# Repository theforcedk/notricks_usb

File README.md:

# notricks_usb
Pentest USB

Order the boards here http://dirtypcbs.com/store/designer/details/8489/1041/atmega32u4-development-board or upload to OSH Park

Download the Sparkfun bootloader (Caterina-promicro16.hex) located at https://github.com/dudanov/sparkfun-promicro-caterina-bootloader/tree/e15665e847b4d9003d69fccb293572aa5e1aae71

```
Burn fuses for external crystal (0 devision)
*Extended*: 0xcb
*High*: 0xd8
*Low*: 0xff
```

```
avrdude -p atmega32u4 -c atmelice_isp -U flash:w:Caterina-promicro16.hex -U efuse:w:0xcb:m -U hfuse:w:0xd8:m -U lfuse:w:0xff:m
```

Open the schematic in EAGLE for actual package sizes, but in general: resistors = 0603, capacitors = 0805

```
1x Atmega32u4 IC
2x 22R resistor
2x 1K resistor
1x 10K resistor
7x 100nF capacitor
1x 1uF capacitor
1x 10uF capacitor
2x LEDs
1x 16MHz crystal
2x 22pF capacitor
1x 2x3 header
Optional: 2x SMD jumper for HWB+VCC
```

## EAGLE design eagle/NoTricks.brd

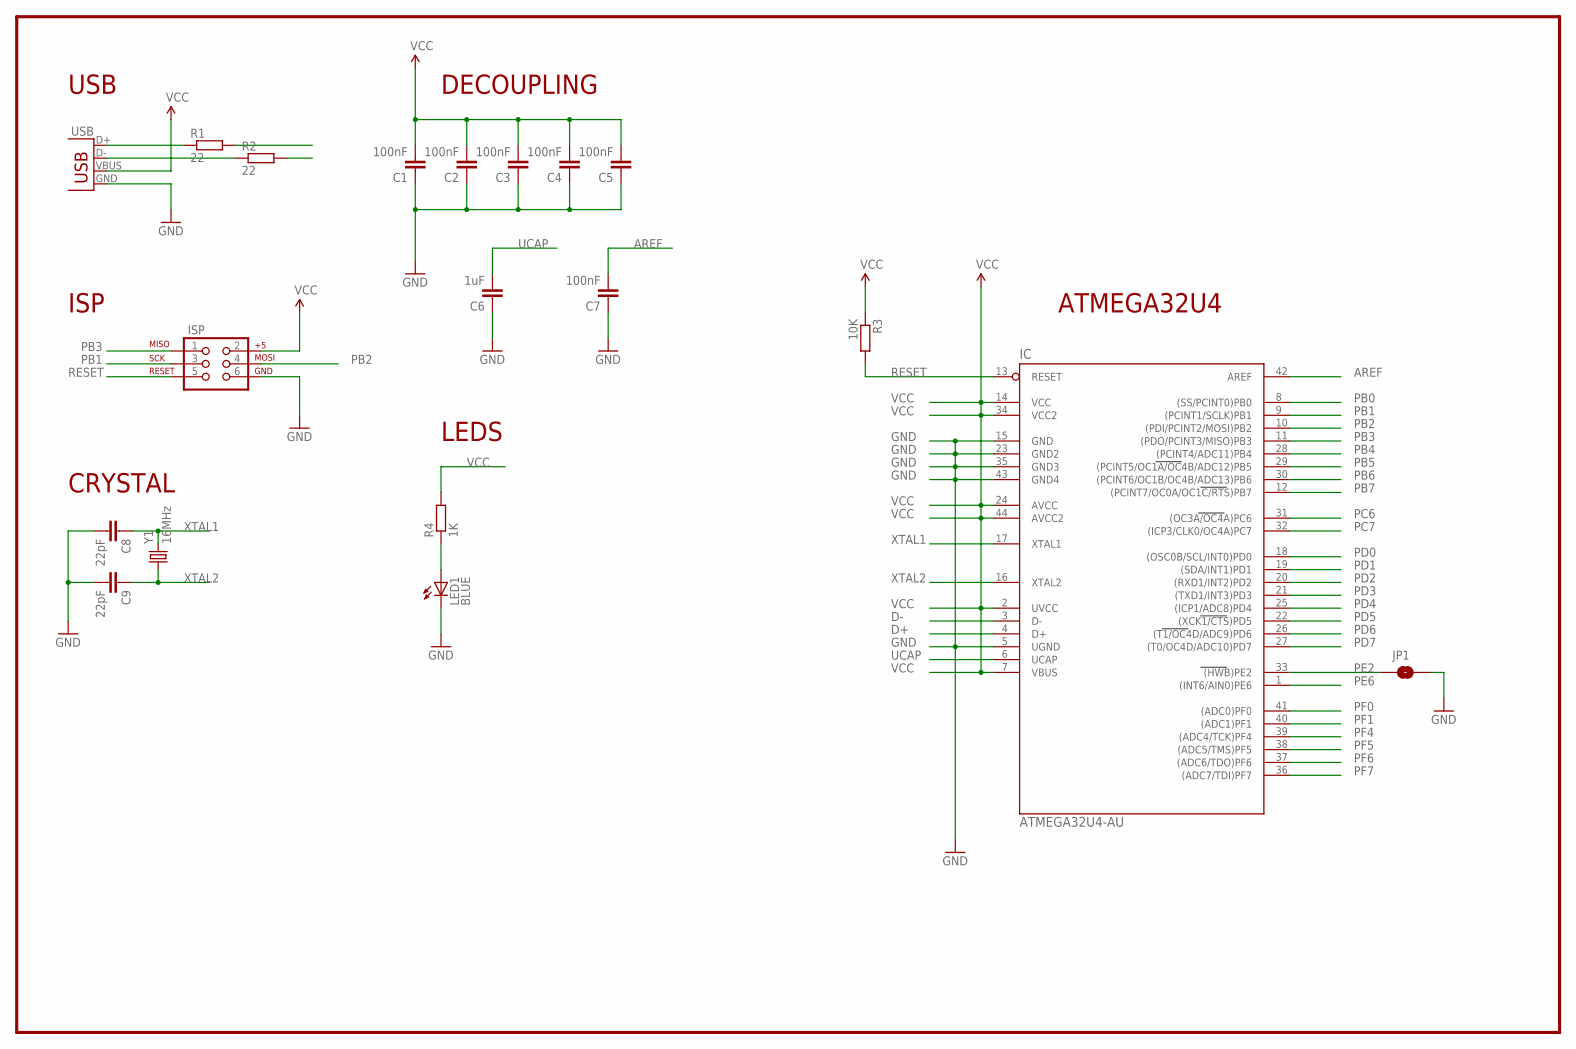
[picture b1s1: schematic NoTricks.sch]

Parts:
C1, C2, C3, C4, C5, C7: 100nF; C0805
C6: 1uF; C0805
C8, C9: 22pF; C0805
IC: ATMEGA32U4-AU; TQFP44
ISP: AVR_SPI_PRG_6PTH; 2X3
JP1: JUMPER-PAD-2-NO; PAD-JUMPER-2-NO_NO_SILK
LED1: BLUE; LED-1206
R1, R2: 22; R0603
R3: 10K; R0603
R4: 1K; R0603
USB: USB-A-H
Y1: 16MHz; CRYSTAL-SMD-5X3

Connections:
AREF: C7.2, IC.42 (AREF)
D+: IC.4 (D+), R1.2
D-: IC.3 (D-), R2.2
GND: C1.1, C2.1, C3.1, C4.1, C5.1, C6.1, C7.1, C8.2, C9.2, IC.5 (UGND), IC.15 (GND), IC.23 (GND2), IC.35 (GND3), IC.43 (GND4), ISP.6, JP1.2, LED1.C, USB.GND
unnamed: R1.1, USB.D+
unnamed: LED1.A, R4.1
unnamed: R2.1, USB.D-
PB0: IC.8 ((SS/PCINT0)PB0)
PB1: IC.9 ((PCINT1/SCLK)PB1), ISP.3
PB2: IC.10 ((PDI/PCINT2/MOSI)PB2), ISP.4
PB3: IC.11 ((PDO/PCINT3/MISO)PB3), ISP.1
PB4: IC.28 ((PCINT4/ADC11)PB4)
PB5: IC.29 ((PCINT5/OC1A/OC4B/ADC12)PB5)
PB6: IC.30 ((PCINT6/OC1B/OC4B/ADC13)PB6)
PB7: IC.12 ((PCINT7/OC0A/OC1C/RTS)PB7)
PC6: IC.31 ((OC3A/OC4A)PC6)
PC7: IC.32 ((ICP3/CLK0/OC4A)PC7)
PD0: IC.18 ((OSC0B/SCL/INT0)PD0)
PD1: IC.19 ((SDA/INT1)PD1)
PD2: IC.20 ((RXD1/INT2)PD2)
PD3: IC.21 ((TXD1/INT3)PD3)
PD4: IC.25 ((ICP1/ADC8)PD4)
PD5: IC.22 ((XCK1/CTS)PD5)
PD6: IC.26 ((T1/OC4D/ADC9)PD6)
PD7: IC.27 ((T0/OC4D/ADC10)PD7)
PE2: IC.33 ((HWB)PE2), JP1.1
PE6: IC.1 ((INT6/AIN0)PE6)
PF0: IC.41 ((ADC0)PF0)
PF1: IC.40 ((ADC1)PF1)
PF4: IC.39 ((ADC4/TCK)PF4)
PF5: IC.38 ((ADC5/TMS)PF5)
PF6: IC.37 ((ADC6/TDO)PF6)
PF7: IC.36 ((ADC7/TDI)PF7)
RESET: IC.13 (RESET), ISP.5, R3.2
UCAP: C6.2, IC.6 (UCAP)
VCC: C1.2, C2.2, C3.2, C4.2, C5.2, IC.2 (UVCC), IC.7 (VBUS), IC.14 (VCC), IC.24 (AVCC), IC.34 (VCC2), IC.44 (AVCC2), ISP.2, R3.1, R4.2, USB.VBUS
XTAL1: C8.1, IC.17 (XTAL1), Y1.3 (2)
XTAL2: C9.1, IC.16 (XTAL2), Y1.1

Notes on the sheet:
ATMEGA32U4
DECOUPLING
USB
ISP
CRYSTAL
LEDS

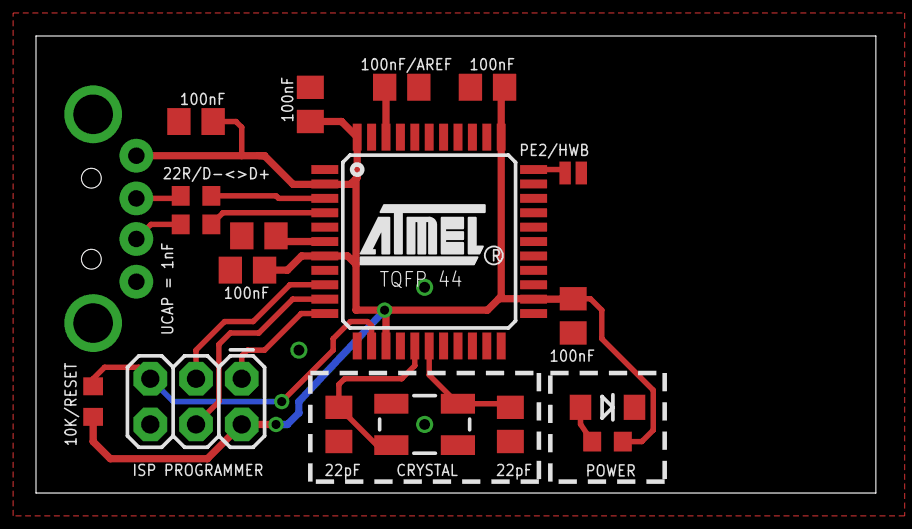
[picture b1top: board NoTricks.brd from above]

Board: 2 copper layers, 46.7 x 25.4 mm, 19 parts (1 on the bottom side), 16 nets.

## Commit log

2017-06-11 init

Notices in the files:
parts and their libraries:
SparkFun-Connectors: Licensing: Creative Commons ShareAlike 4.0 International - https://creativecommons.org/licenses/by-sa/4.0
